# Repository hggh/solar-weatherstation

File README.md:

# yet another weatherstation

 * ESP32
   *  rain gauge
   *  wind speed sensor
   *  BME280
 * ESP8266 (with Feinstaub sensor firmware)
   * SDS 011

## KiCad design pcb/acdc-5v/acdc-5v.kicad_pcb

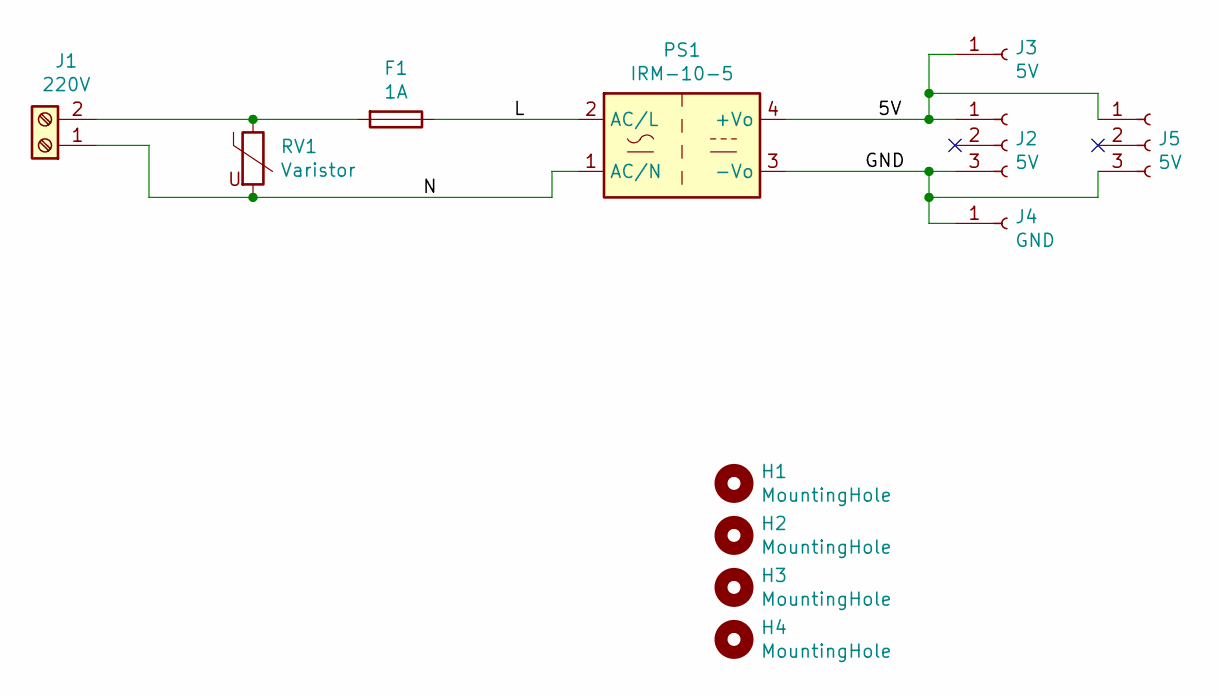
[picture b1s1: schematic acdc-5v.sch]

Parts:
F1: 1A; Fuseholder_Cylinder-5x20mm_Schurter_0031_8201_Horizontal_Op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
H1, H2, H3, H4: MountingHole; MountingHole_3.2mm_M3
J1: 220V; RND_Schraubklemme_2pol
J2, J5: 5V; PinHeader_1x03_P2.54mm_Horizontal
J3: 5V; PinHeader_1x01_P2.54mm_Vertical
J4: GND; PinHeader_1x01_P2.54mm_Vertical
PS1: IRM-10-5; Converter_ACDC_MeanWell_IRM-10-xx_THT
RV1: Varistor; RV_Disc_D12mm_W4.2mm_P7.5mm

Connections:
/5V: J2.1, J3.1, J5.1, PS1.4 (+Vo)
/GND: J2.3, J4.1, J5.3, PS1.3 (-Vo)
/L: F1.1, PS1.2 (AC/L)
/N: J1.1, PS1.1 (AC/N), RV1.2
unnamed: F1.2, J1.2, RV1.1

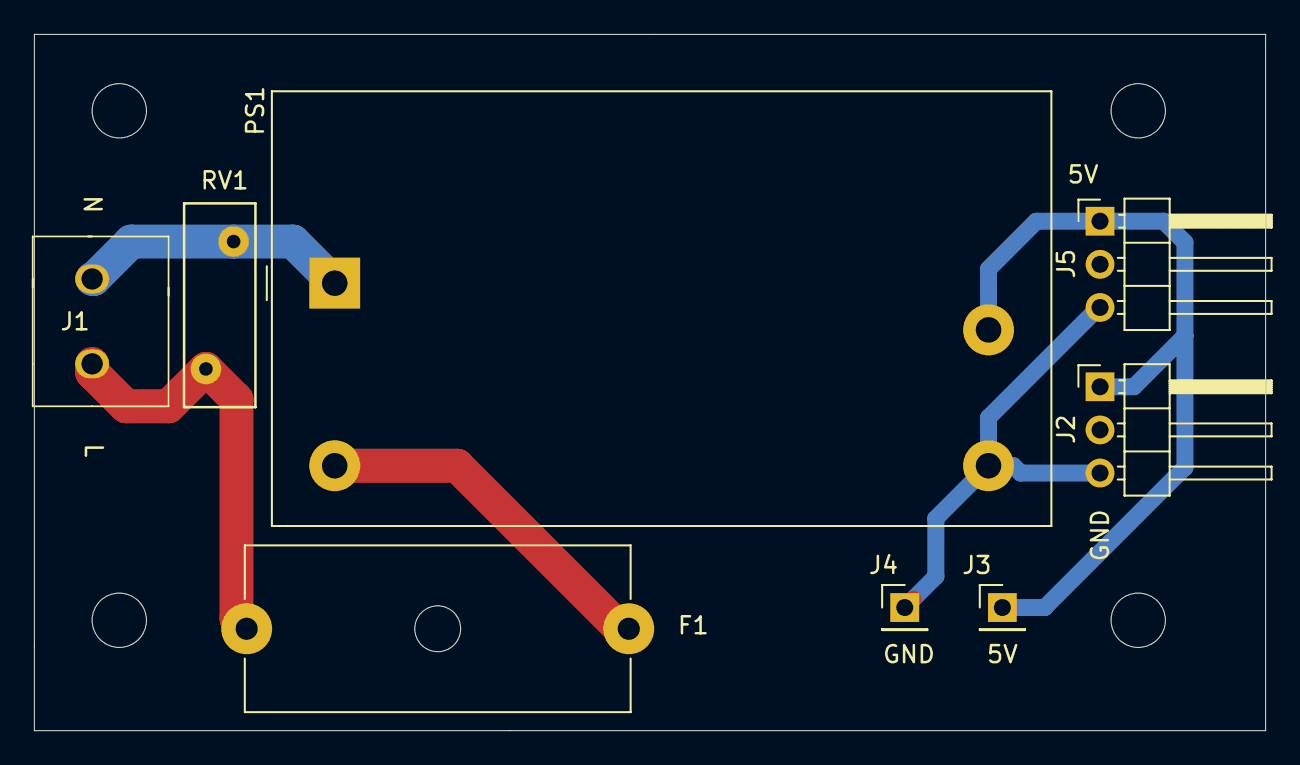
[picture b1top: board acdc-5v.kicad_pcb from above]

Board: 2 copper layers, 72.5 x 41.0 mm, 12 parts (0 on the bottom side), 5 nets.

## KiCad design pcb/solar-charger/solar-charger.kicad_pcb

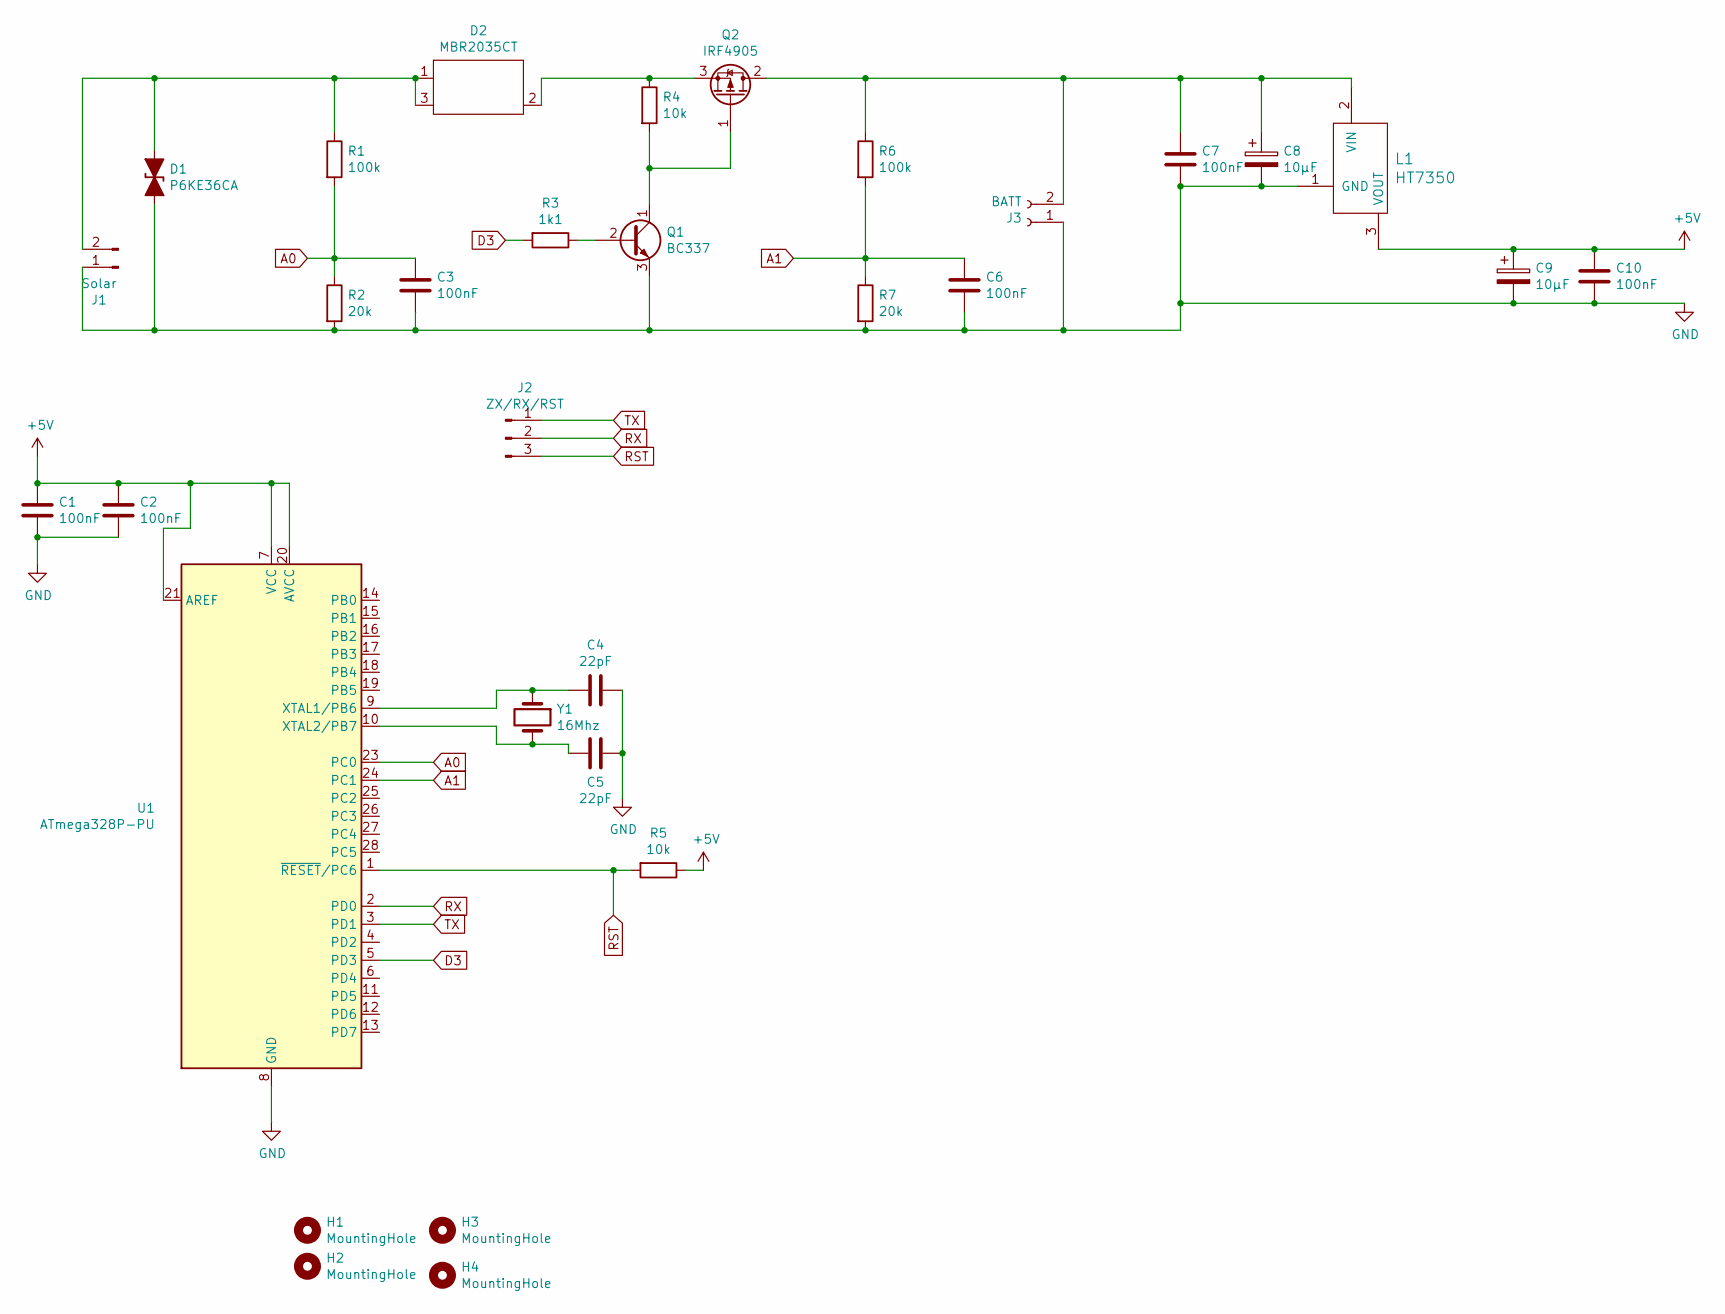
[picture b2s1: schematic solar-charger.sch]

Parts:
C1, C2, C3, C6, C7, C10: 100nF; C_0805_2012Metric_Pad1.18x1.45mm_HandSolder
C4, C5: 22pF; C_0805_2012Metric_Pad1.18x1.45mm_HandSolder
C8, C9: 10µF; CP_Radial_D4.0mm_P2.00mm
D1: P6KE36CA; D_A-405_P10.16mm_Horizontal
D2: MBR2035CT; TO-220-3_Vertical
H1, H2, H3, H4: MountingHole; MountingHole_3.2mm_M3
J1: Solar; JST_PH_S2B-PH-K_1x02_P2.00mm_Horizontal
J2: ZX/RX/RST; PinHeader_1x03_P2.54mm_Vertical
J3: BATT; JST_PH_S2B-PH-K_1x02_P2.00mm_Horizontal
L1: HT7350; TO-92
Q1: BC337; TO-92_Inline
Q2: IRF4905; TO-220-3_Vertical
R1, R6: 100k; R_Axial_DIN0207_L6.3mm_D2.5mm_P7.62mm_Horizontal
R2, R7: 20k; R_Axial_DIN0207_L6.3mm_D2.5mm_P7.62mm_Horizontal
R3: 1k1; R_0805_2012Metric_Pad1.20x1.40mm_HandSolder
R4, R5: 10k; R_0805_2012Metric_Pad1.20x1.40mm_HandSolder
U1: ATmega328P-PU; DIP-28_W7.62mm
Y1: 16Mhz; Crystal_HC49-U_Vertical

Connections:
+5V: C1.1, C2.1, C9.1, C10.1, L1.3 (VOUT), R5.1, U1.7 (VCC), U1.20 (AVCC), U1.21 (AREF)
A0: C3.1, R1.2, R2.1, U1.23 (PC0)
A1: C6.1, R6.2, R7.1, U1.24 (PC1)
D3: R3.2, U1.5 (PD3)
GND: C1.2, C2.2, C3.2, C4.1, C5.2, C6.2, C7.2, C8.2, C9.2, C10.2, D1.2 (A2), J1.1, J3.1, L1.1 (GND), Q1.3 (E), R2.2, R7.2, U1.8 (GND), U1.22 (GND)
unnamed: C4.2, U1.9 (XTAL1/PB6), Y1.1
unnamed: C5.1, U1.10 (XTAL2/PB7), Y1.2
unnamed: C7.1, C8.1, J3.2, L1.2 (VIN), Q2.2 (D), R6.1
unnamed: D1.1 (A1), D2.1, D2.3, J1.2, R1.1
unnamed: D2.2, Q2.3 (S), R4.1
unnamed: Q1.1 (C), Q2.1 (G), R4.2
unnamed: Q1.2 (B), R3.1
RST: J2.3, R5.2, U1.1 (~RESET~/PC6)
RX: J2.2, U1.2 (PD0)
TX: J2.1, U1.3 (PD1)

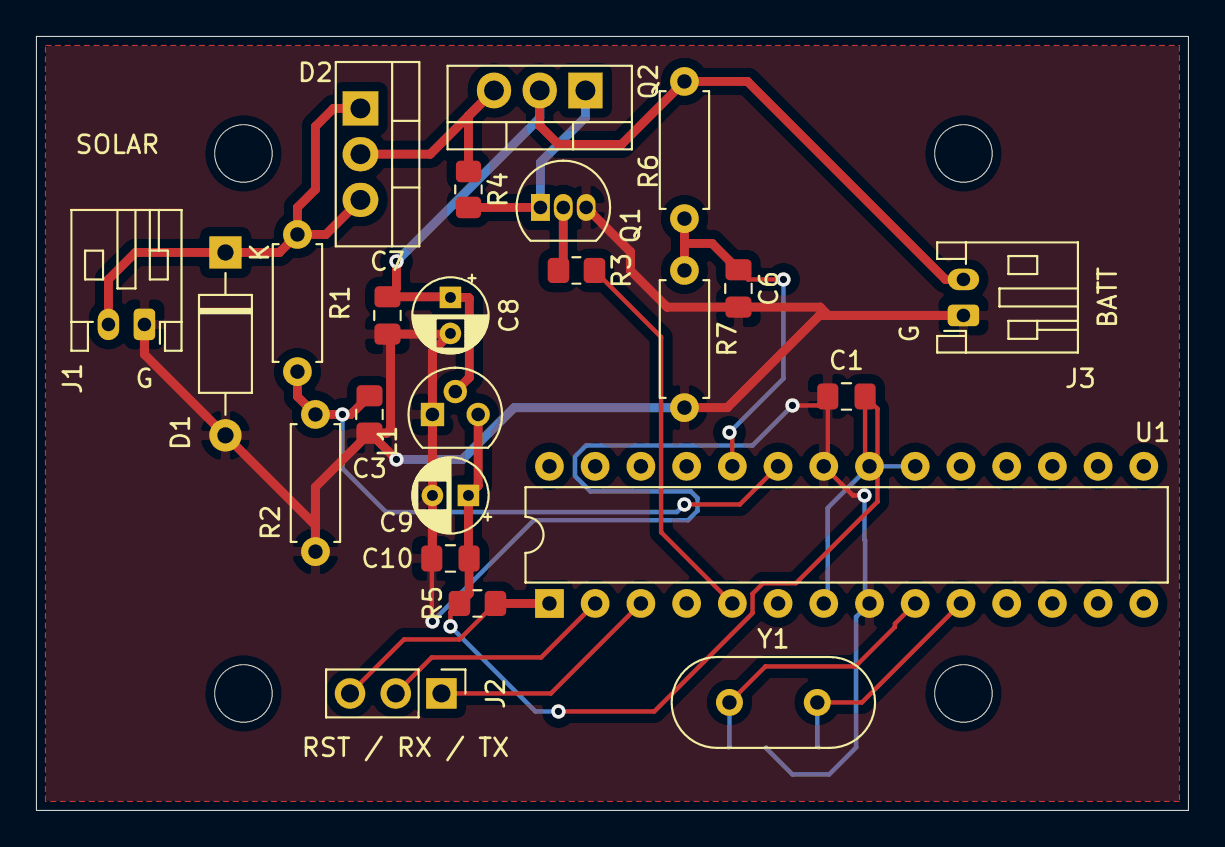
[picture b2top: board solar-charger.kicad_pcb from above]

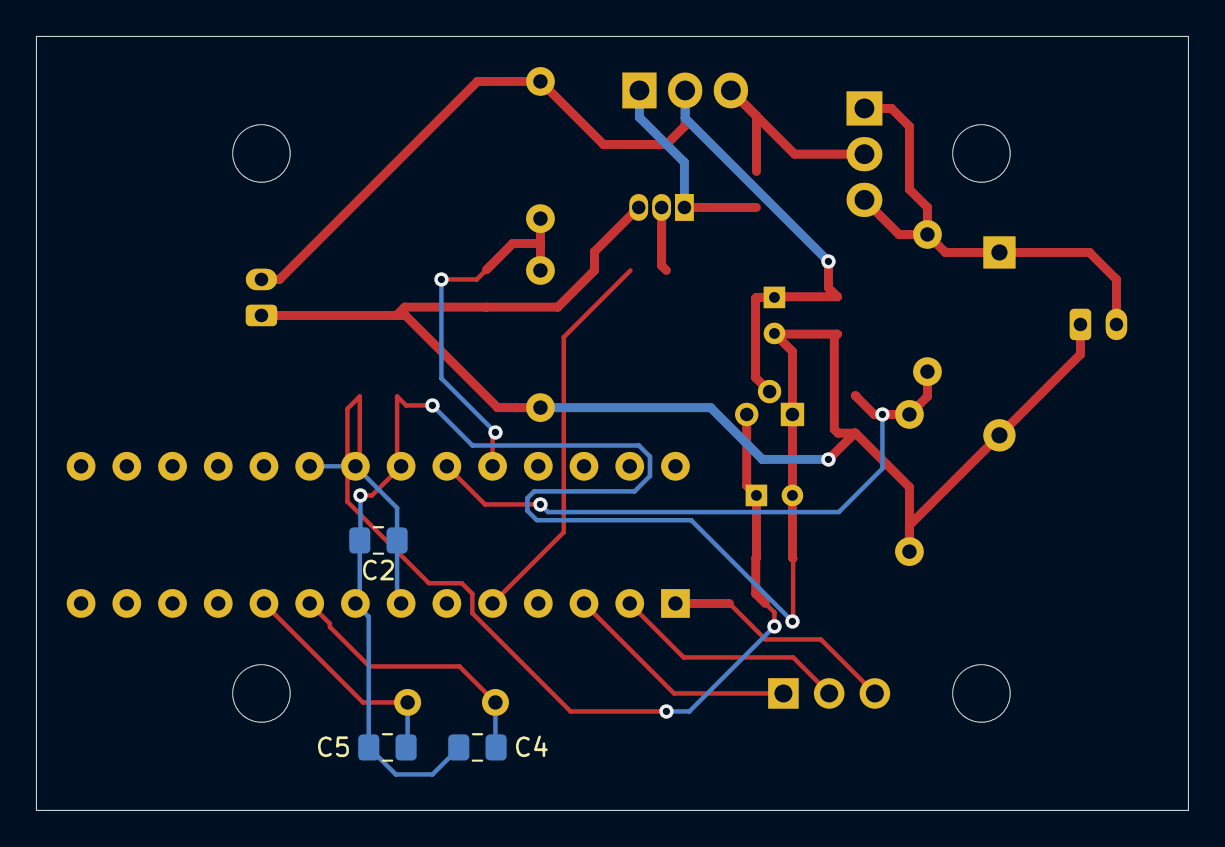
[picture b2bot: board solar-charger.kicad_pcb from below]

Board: 2 copper layers, 64.0 x 43.0 mm, 31 parts (3 on the bottom side), 15 nets.

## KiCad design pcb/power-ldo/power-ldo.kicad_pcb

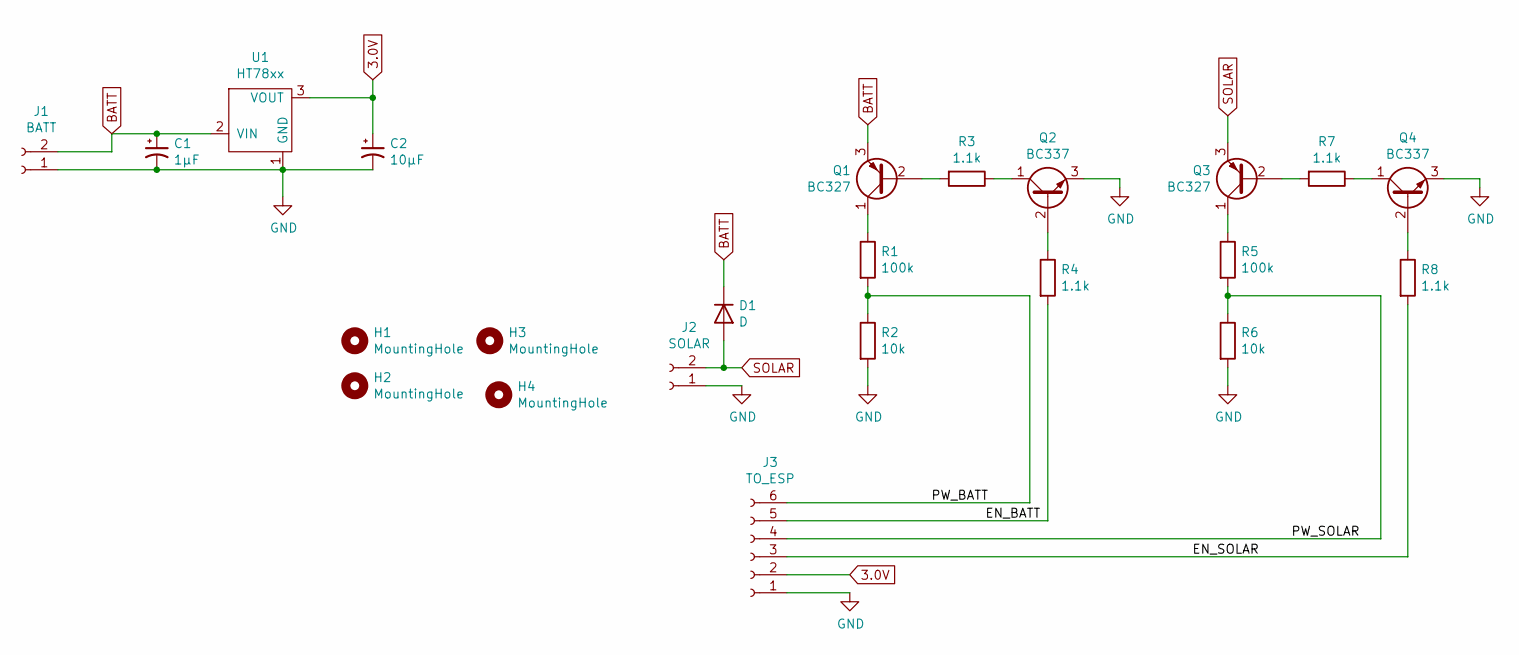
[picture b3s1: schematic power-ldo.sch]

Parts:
C1: 1µF; CP_Elec_4x5.4
C2: 10µF; CP_Elec_4x5.4
D1: D; D_DO-41_SOD81_P7.62mm_Horizontal
H1, H2, H3, H4: MountingHole; MountingHole_3.2mm_M3
J1: BATT; JST_PH_S2B-PH-K_1x02_P2.00mm_Horizontal
J2: SOLAR; JST_PH_S2B-PH-K_1x02_P2.00mm_Horizontal
J3: TO_ESP; PinSocket_2x03_P2.54mm_Vertical
Q1, Q3: BC327; TO-92_Inline
Q2, Q4: BC337; TO-92_Inline
R1, R5: 100k; R_0805_2012Metric
R2, R6: 10k; R_0805_2012Metric
R3, R4, R7, R8: 1.1k; R_0805_2012Metric
U1: HT78xx; SOT-89-3

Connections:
3.0V: C2.1, J3.2, U1.3 (VOUT)
/EN_BATT: J3.5, R4.2
/EN_SOLAR: J3.3, R8.2
/PW_BATT: J3.6, R1.2, R2.1
/PW_SOLAR: J3.4, R5.2, R6.1
BATT: C1.1, D1.1 (K), J1.2, Q1.3 (E), U1.2 (VIN)
GND: C1.2, C2.2, J1.1, J2.1, J3.1, Q2.3 (E), Q4.3 (E), R2.2, R6.2, U1.1 (GND)
unnamed: Q1.1 (C), R1.1
unnamed: Q1.2 (B), R3.2
unnamed: Q2.1 (C), R3.1
unnamed: Q2.2 (B), R4.1
unnamed: Q3.1 (C), R5.1
unnamed: Q3.2 (B), R7.2
unnamed: Q4.1 (C), R7.1
unnamed: Q4.2 (B), R8.1
SOLAR: D1.2 (A), J2.2, Q3.3 (E)

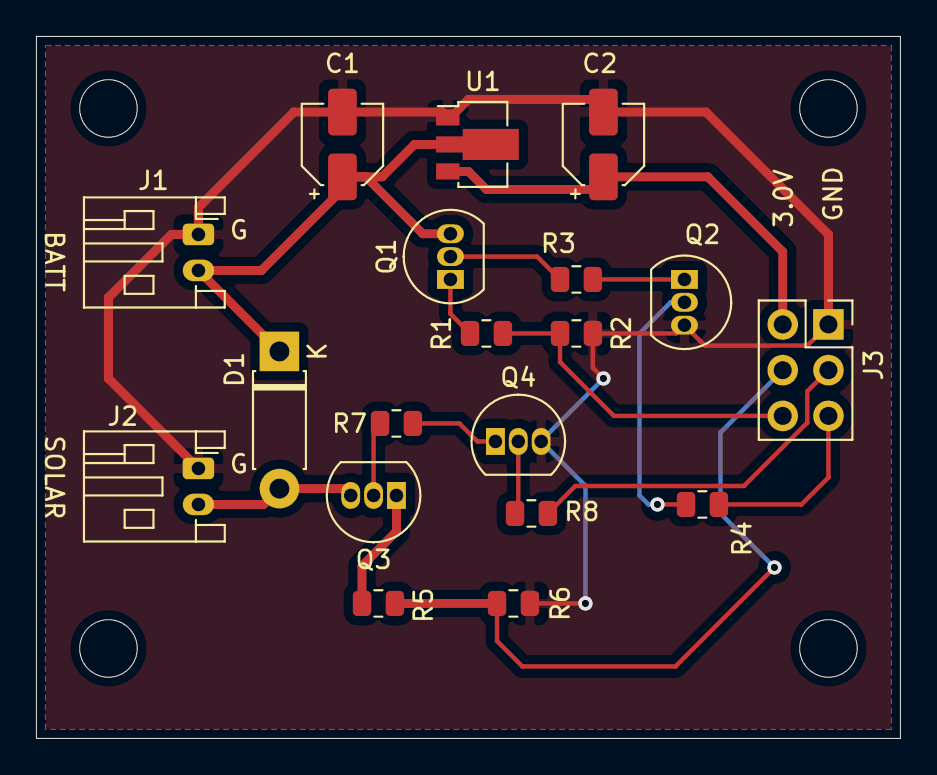
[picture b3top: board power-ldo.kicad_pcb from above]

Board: 2 copper layers, 48.0 x 39.0 mm, 23 parts (0 on the bottom side), 16 nets.

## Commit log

2017-08-21 initial source code
2017-08-21 sleep time
2017-08-21 added dht22 type
2017-08-21 added pcb for solar /supercap
2017-09-07 read voltage from solar panel
2017-09-07 added 51k/10k for solar power to atmel
2017-09-07 added r values for reading solar power
2018-04-11 removed voltage check
2018-04-21 power_adc_disable does not work use ADCSRA; disable BOD
2018-04-22 use jeelib
2018-05-04 new pcb
2018-05-06 added sending voltage
2018-05-06 updated schema
2018-05-06 added NTC 10k
2018-05-08 added NTC for supercap temperature monitoring
2018-05-10 added try for a better case
2018-05-10 added adc enable/disable methods
2018-05-12 read the voltage of the solar panel
2018-05-13 updated todo
2018-05-15 updated svg to 6mm
2019-04-29 move to PlatformIO
2019-05-04 updated env name
2019-05-11 added rain gauge, just count the clicks
2020-02-06 holder for rain
2020-02-07 update holder
2021-01-08 add STL
2021-01-08 remove old stuff
2021-01-21 add ldo pcb
2021-01-25 final pcb
2021-02-10 remove old pcbs
2021-04-01 add new 220V to 5V 2A block
2021-04-01 update pcb
2021-04-23 add cases
